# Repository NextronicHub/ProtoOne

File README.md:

# Nextronic ProtoOne

The protoOne is an Arduino Uno prototyping shield with a small soldering area, two general LEDs, Bluetooth Pinout, a general pushbutton switch, and the reset switch 
<br />This board is based on the sparkfun [ProtoShield](http://www.sparkfun.com/products/11665).

##Repository Contents

/Hardware - Design files (.brd, .sch)
<br />/Documentation - datasheet and examples

##Product Versions

ProtoOne_V1 first release

##License Information

The hardware is released under [Creative Commons ShareAlike 4.0 International](https://creativecommons.org/licenses/by-sa/4.0/).

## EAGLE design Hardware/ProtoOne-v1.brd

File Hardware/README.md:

#  Nextronic ProtoOne Design Files

The .sch and .brd files are Eagle CAD schematic and PCB design files from Nextronic.  
Eagle PCB Design | Schematic Editor, Layout Editor & Autorouter can be found at http://www.autodesk.com/products/eagle.

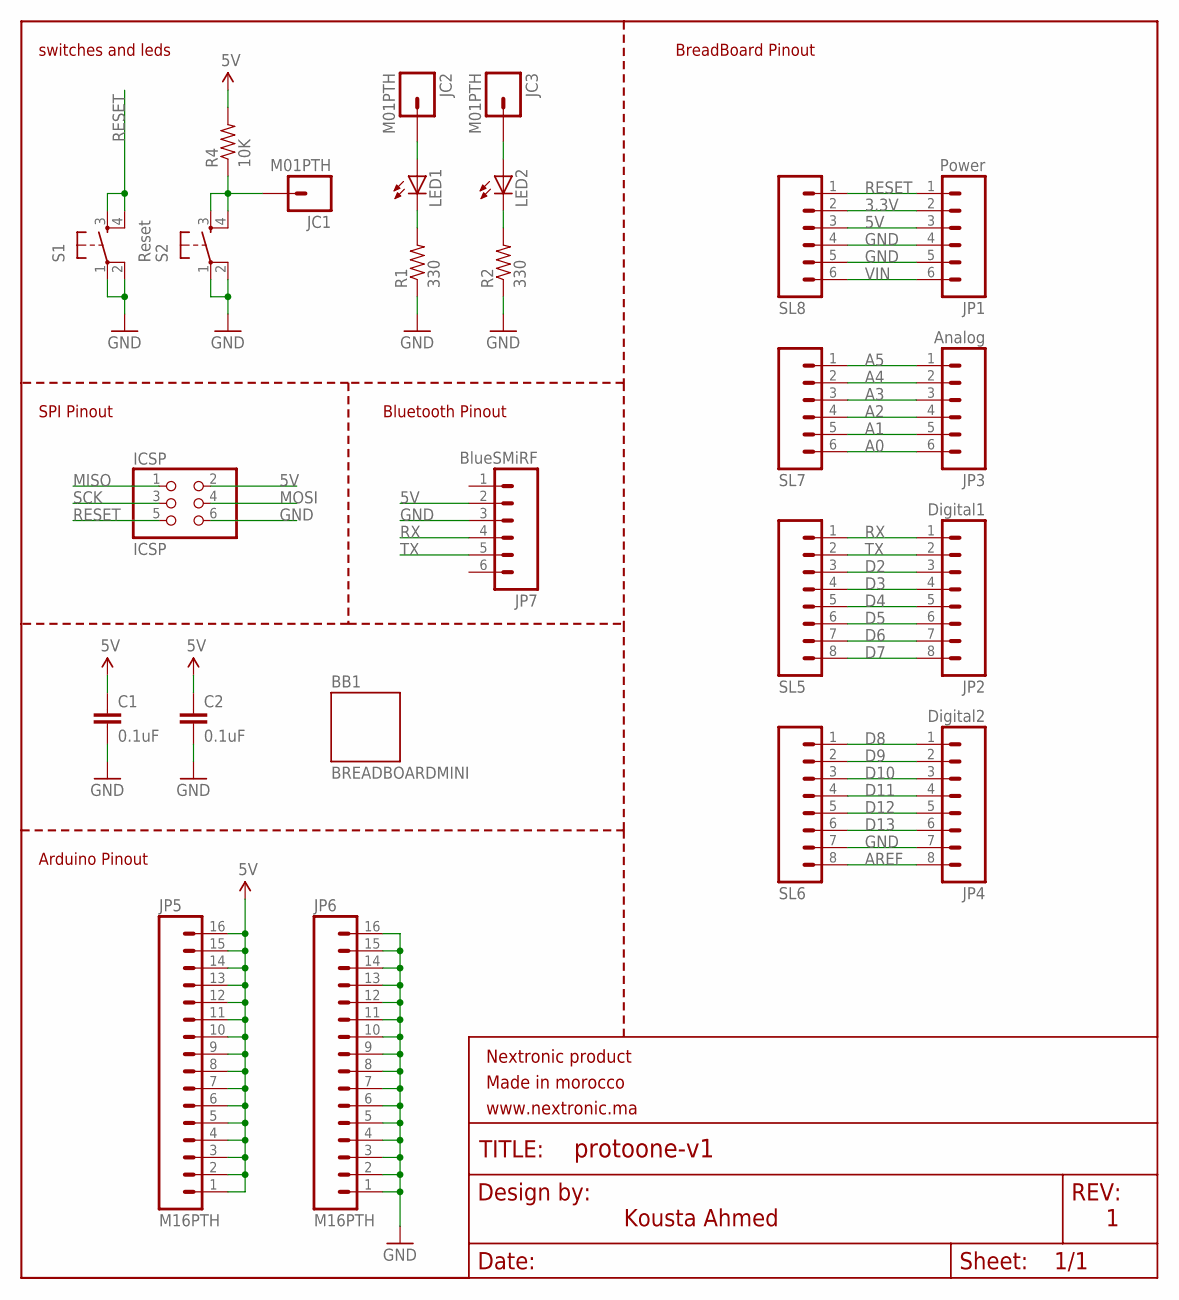
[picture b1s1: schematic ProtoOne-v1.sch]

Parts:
BB1: BREADBOARDMINI; BREADBOARD-MINI
C1, C2: 0.1uF; CAP-PTH-SMALL2; MPN MC0805B104K500A5.08MM
FRAME1: FRAME-LETTER; CREATIVE_COMMONS
ICSP: ICSP; 2X03
JC1, JC2, JC3: M01PTH; 1X01
JP1: Power; 1X06
JP2: Digital1; 1X08
JP3: Analog; 1X06
JP4: Digital2; 1X08
JP5, JP6: M16PTH; 1X16
JP7: BlueSMiRF; 1X06
LED1, LED2: LED5MM
R1, R2: 330; AXIAL-0.3
R4: 10K; AXIAL-0.3; MPN RR0816P-103-B-T5
S1: Reset; TACTILE-PTH
S2: TAC_SWITCHPTH; TACTILE-PTH
SL5, SL6: M08; 1X08
SL7, SL8: M06SIP; 1X06

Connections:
3.3V: JP1.2, SL8.2
5V: C1.1, C2.1, ICSP.2, JP1.3, JP5.1, JP5.2, JP5.3, JP5.4, JP5.5, JP5.6, JP5.7, JP5.8, JP5.9, JP5.10, JP5.11, JP5.12, JP5.13, JP5.14, JP5.15, JP5.16, JP7.2, R4.P$2 (2), SL8.3
A0: JP3.6, SL7.6
A1: JP3.5, SL7.5
A2: JP3.4, SL7.4
A3: JP3.3, SL7.3
A4: JP3.2, SL7.2
A5: JP3.1, SL7.1
AREF: JP4.8, SL6.8
D2: JP2.3, SL5.3
D3: JP2.4, SL5.4
D4: JP2.5, SL5.5
D5: JP2.6, SL5.6
D6: JP2.7, SL5.7
D7: JP2.8, SL5.8
D8: JP4.1, SL6.1
D9: JP4.2, SL6.2
D10: JP4.3, SL6.3
D11: JP4.4, SL6.4
D12: JP4.5, SL6.5
D13: JP4.6, SL6.6
GND: C1.2, C2.2, ICSP.6, JP1.4, JP1.5, JP4.7, JP6.1, JP6.2, JP6.3, JP6.4, JP6.5, JP6.6, JP6.7, JP6.8, JP6.9, JP6.10, JP6.11, JP6.12, JP6.13, JP6.14, JP6.15, JP6.16, JP7.3, R1.P$1 (1), R2.P$1 (1), S1.1, S1.2, S2.1, S2.2, SL6.7, SL8.4, SL8.5
MISO: ICSP.1
MOSI: ICSP.4
unnamed: JC1.1, R4.P$1 (1), S2.3, S2.4
unnamed: LED1.K (C), R1.P$2 (2)
unnamed: LED2.K (C), R2.P$2 (2)
unnamed: JC2.1, LED1.A
unnamed: JC3.1, LED2.A
RESET: ICSP.5, JP1.1, S1.3, S1.4, SL8.1
RX: JP2.1, JP7.4, SL5.1
SCK: ICSP.3
TX: JP2.2, JP7.5, SL5.2
VIN: JP1.6, SL8.6

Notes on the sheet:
Kousta Ahmed
Arduino Pinout
BreadBoard Pinout
Bluetooth Pinout
SPI Pinout
switches and leds

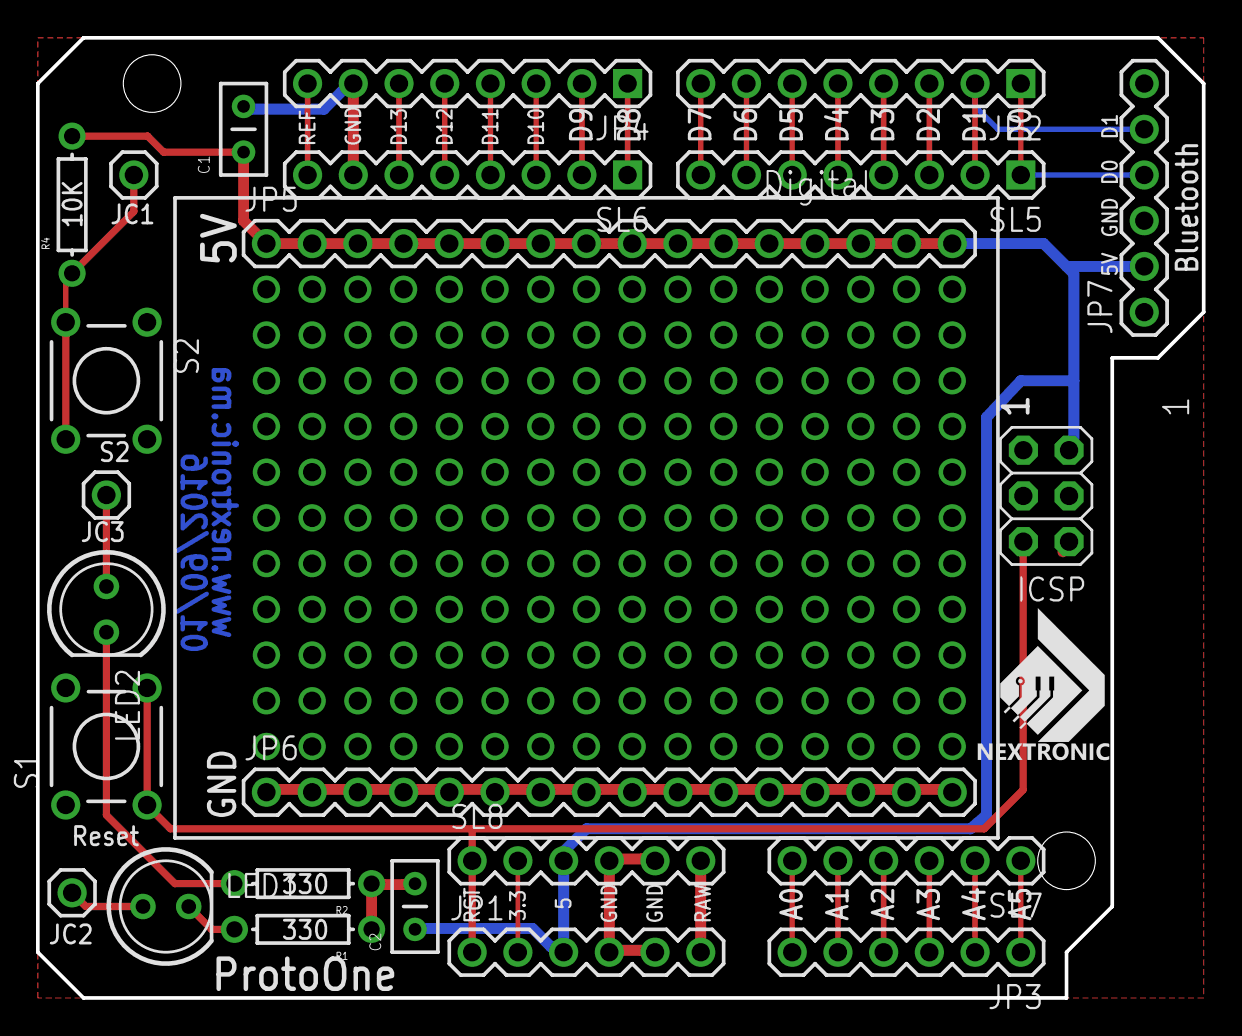
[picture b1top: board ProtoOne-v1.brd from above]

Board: 2 copper layers, 64.8 x 53.3 mm, 26 parts (0 on the bottom side), 31 nets.

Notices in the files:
parts and their libraries:
SparkFun-Aesthetics: Licensing: Creative Commons ShareAlike 4.0 International - https://creativecommons.org/licenses/by-sa/4.0
